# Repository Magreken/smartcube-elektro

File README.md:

# smartcube-elektro
Elektrotechnikteil der Diplomarbeit

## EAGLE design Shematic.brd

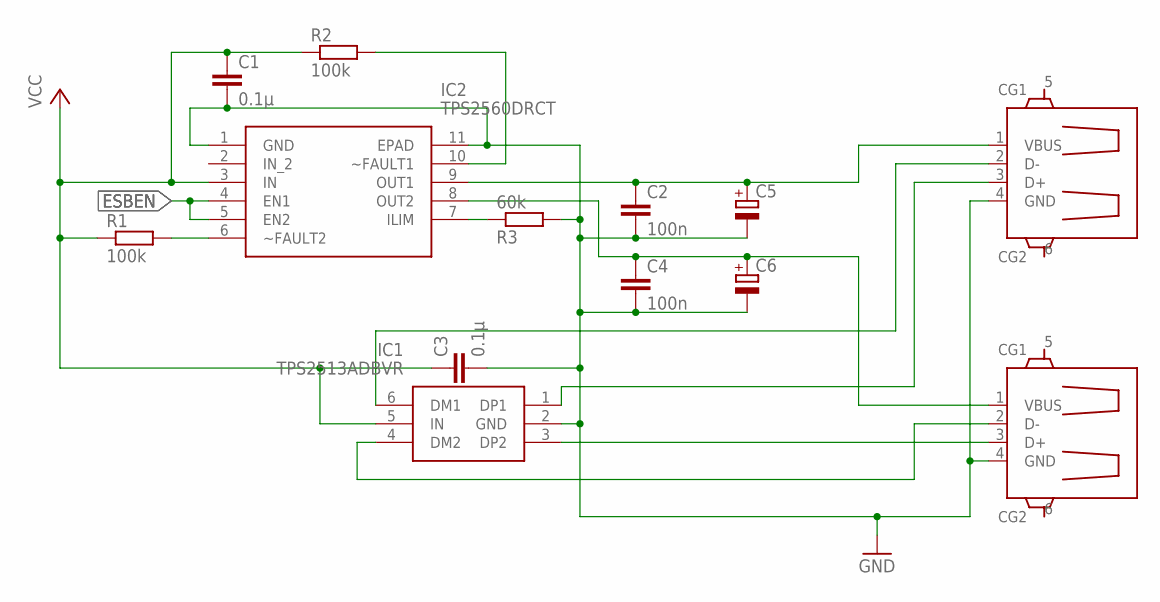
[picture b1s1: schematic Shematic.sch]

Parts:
C1: 0.1µ; C0805
C2, C4: 100n; C1206
C3: 0.1µ; C1206
C5, C6: CPOL-EU150CLZ-1010; 150CLZ-1010
IC1: TPS2513ADBVR; SOT95P280X145-6N
IC2: TPS2560DRCT; SON50P300X300X100-11N
R1, R2: 100k; R1206
R3: 60k; R1206
X1, X2: GHI2_USB_HOST_W/CHASSIS_GND; GHI2_USB_HOST_HORIZONTAL_W/CHASSIS_GND

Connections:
DM2: IC1.4 (DM2), X2.2 (D-)
DP2: IC1.3 (DP2), X2.3 (D+)
ESBEN: IC2.4 (EN1), IC2.5 (EN2)
GND: C1.2, C2.2, C3.2, C4.2, C5.-, C6.-, IC1.2 (GND), IC2.1 (GND), IC2.11 (EPAD), R3.2, X1.4 (GND), X2.4 (GND)
ILIM: IC2.7 (ILIM), R3.1
unnamed: IC2.6 (~FAULT2), R1.2
unnamed: IC2.10 (~FAULT1), R2.2
unnamed: C2.1, C5.+, IC2.9 (OUT1), X1.1 (VBUS)
unnamed: IC1.6 (DM1), X1.2 (D-)
unnamed: IC1.1 (DP1), X1.3 (D+)
unnamed: C4.1, C6.+, IC2.8 (OUT2), X2.1 (VBUS)
VCC: C1.1, C3.1, IC1.5 (IN), IC2.3 (IN), R1.1, R2.1

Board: 2 copper layers, 13 parts (0 on the bottom side), 12 nets, no tracks yet.

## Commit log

2019-05-21 Rename README.md to CHANGELOG.md
2019-05-21 Rename CHANGELOG.md to README.md
2019-11-20 Init eagle files
2019-11-20 Refactor project structure
2019-11-25 Updated shematic
